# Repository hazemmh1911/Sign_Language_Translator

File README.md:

# Sign_Language_Translator
 
Our team Graduation project ,it uses arduino nano and processing 3 to translate a physical hardware signals into text on an oled and speech in a speaker.

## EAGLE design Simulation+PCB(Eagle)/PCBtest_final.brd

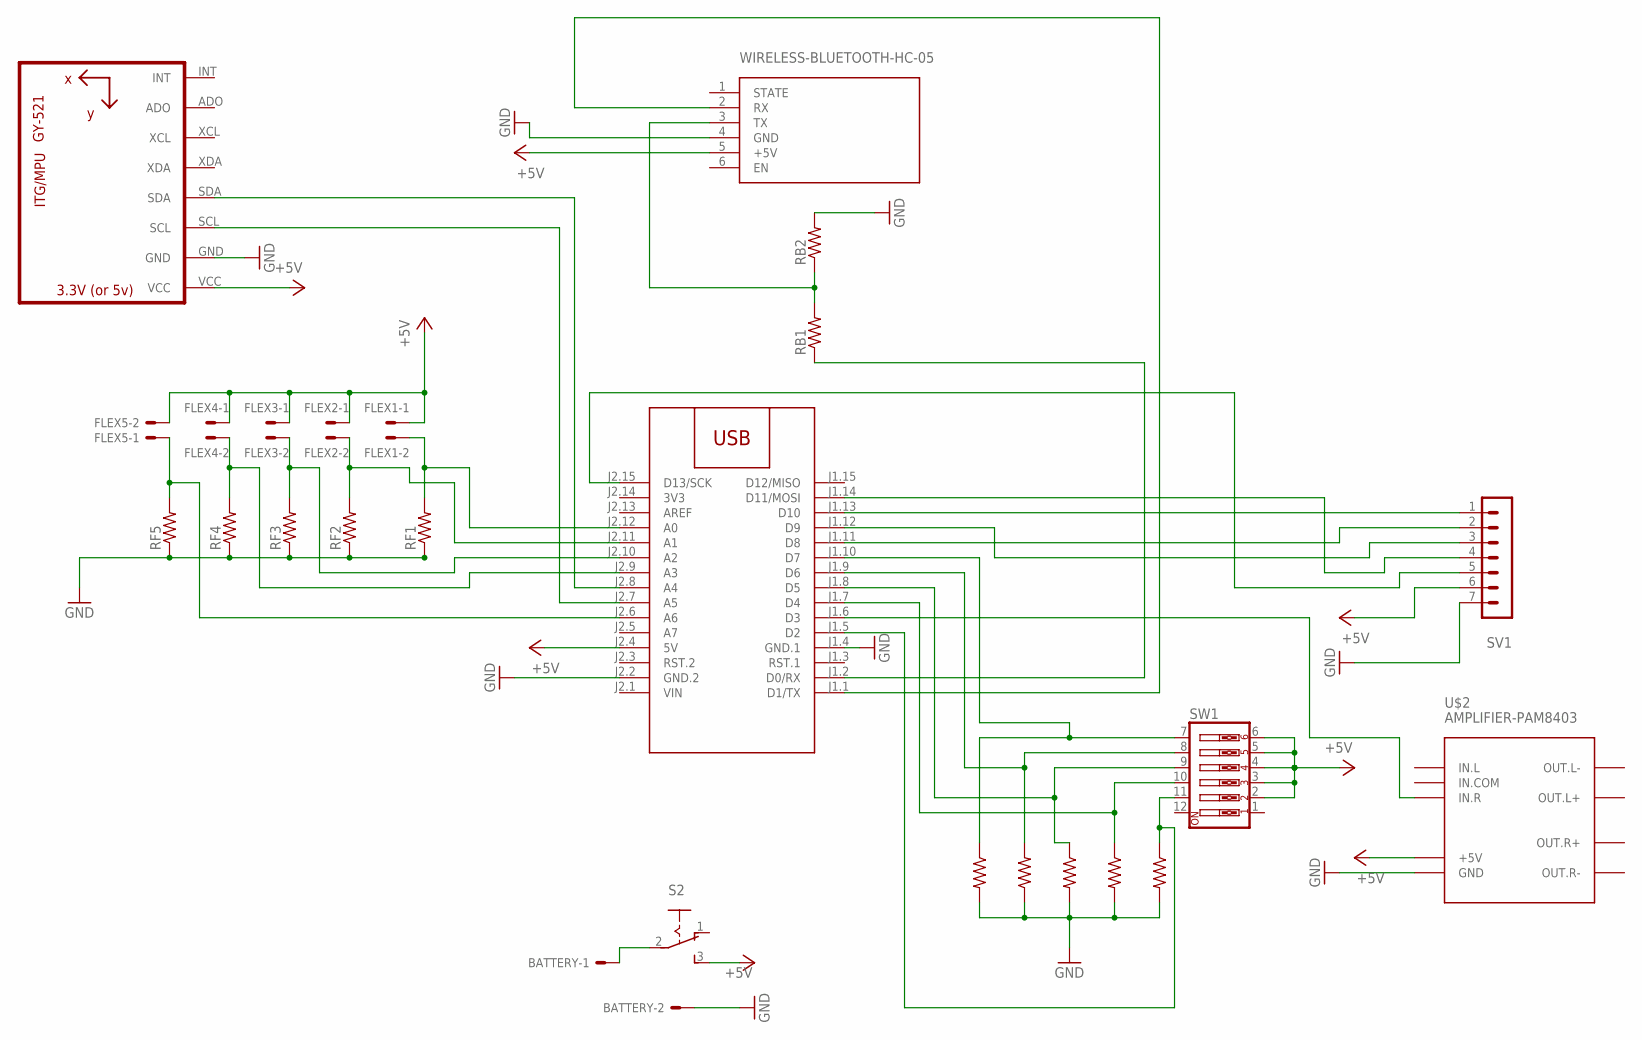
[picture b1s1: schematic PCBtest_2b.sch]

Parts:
BATTERY: 332-02
FLEX1, FLEX2, FLEX3, FLEX4, FLEX5: 332-02
M1: ARDUINO-NANO-3.0
RB1, RB2: R-US_0204/7; 0204/7
RF1, RF2, RF3, RF4, RF5: R-US_0204/7; 0204/7
RS1, RS2, RS3, RS4, RS5: R-US_0204/7; 0204/7
S2: 255SB
SV1: MA07-1
SW1: SW_DIP-6; EDG-06
U1: GY-521MPU6050; GY-521
U$1: WIRELESS-BLUETOOTH-HC-05
U$2: AMPLIFIER-PAM8403

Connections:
3V3: M1.J2.14 (3V3)
+5V: FLEX1.1, FLEX2.1, FLEX3.1, FLEX4.1, FLEX5.2, M1.J2.4 (5V), S2.3 (S), SV1.6, SW1.2, SW1.3, SW1.4, SW1.5, SW1.6, U1.VCC, U$1.5 (+5V), U$2.+5V
GND: BATTERY.2, M1.J1.4 (GND.1), M1.J2.2 (GND.2), RB2.2, RF1.1, RF2.1, RF3.1, RF4.1, RF5.1, RS1.2, RS2.2, RS3.2, RS4.1, RS5.2, SV1.7, U1.GND, U$1.4 (GND), U$2.GND
unnamed: M1.J1.5 (D2), RS1.1, SW1.11
unnamed: FLEX5.1, M1.J2.6 (A6), RF5.2
unnamed: M1.J1.8 (D5), RS3.1, SW1.9
unnamed: FLEX3.2, M1.J2.10 (A2), RF3.2
unnamed: M1.J2.8 (A4), U1.SDA
unnamed: M1.J2.7 (A5), U1.SCL
unnamed: RB1.2, RB2.1, U$1.3 (TX)
unnamed: FLEX1.2, M1.J2.12 (A0), RF1.2
unnamed: M1.J1.6 (D3), U$2.IN.R
unnamed: M1.J1.1 (D1/TX), U$1.2 (RX)
unnamed: M1.J1.2 (D0/RX), RB1.1
unnamed: M1.J1.9 (D6), RS4.2, SW1.8
unnamed: FLEX4.2, M1.J2.9 (A3), RF4.2
unnamed: M1.J1.13 (D10), SV1.1
unnamed: FLEX2.2, M1.J2.11 (A1), RF2.2
unnamed: M1.J1.11 (D8), SV1.2
unnamed: M1.J1.12 (D9), SV1.3
unnamed: BATTERY.1, S2.2
unnamed: M1.J1.14 (D11/MOSI), SV1.4
unnamed: M1.J2.15 (D13/SCK), SV1.5
unnamed: M1.J1.10 (D7), RS5.1, SW1.7
unnamed: M1.J1.7 (D4), RS2.1, SW1.10
VIN: M1.J2.1 (VIN)

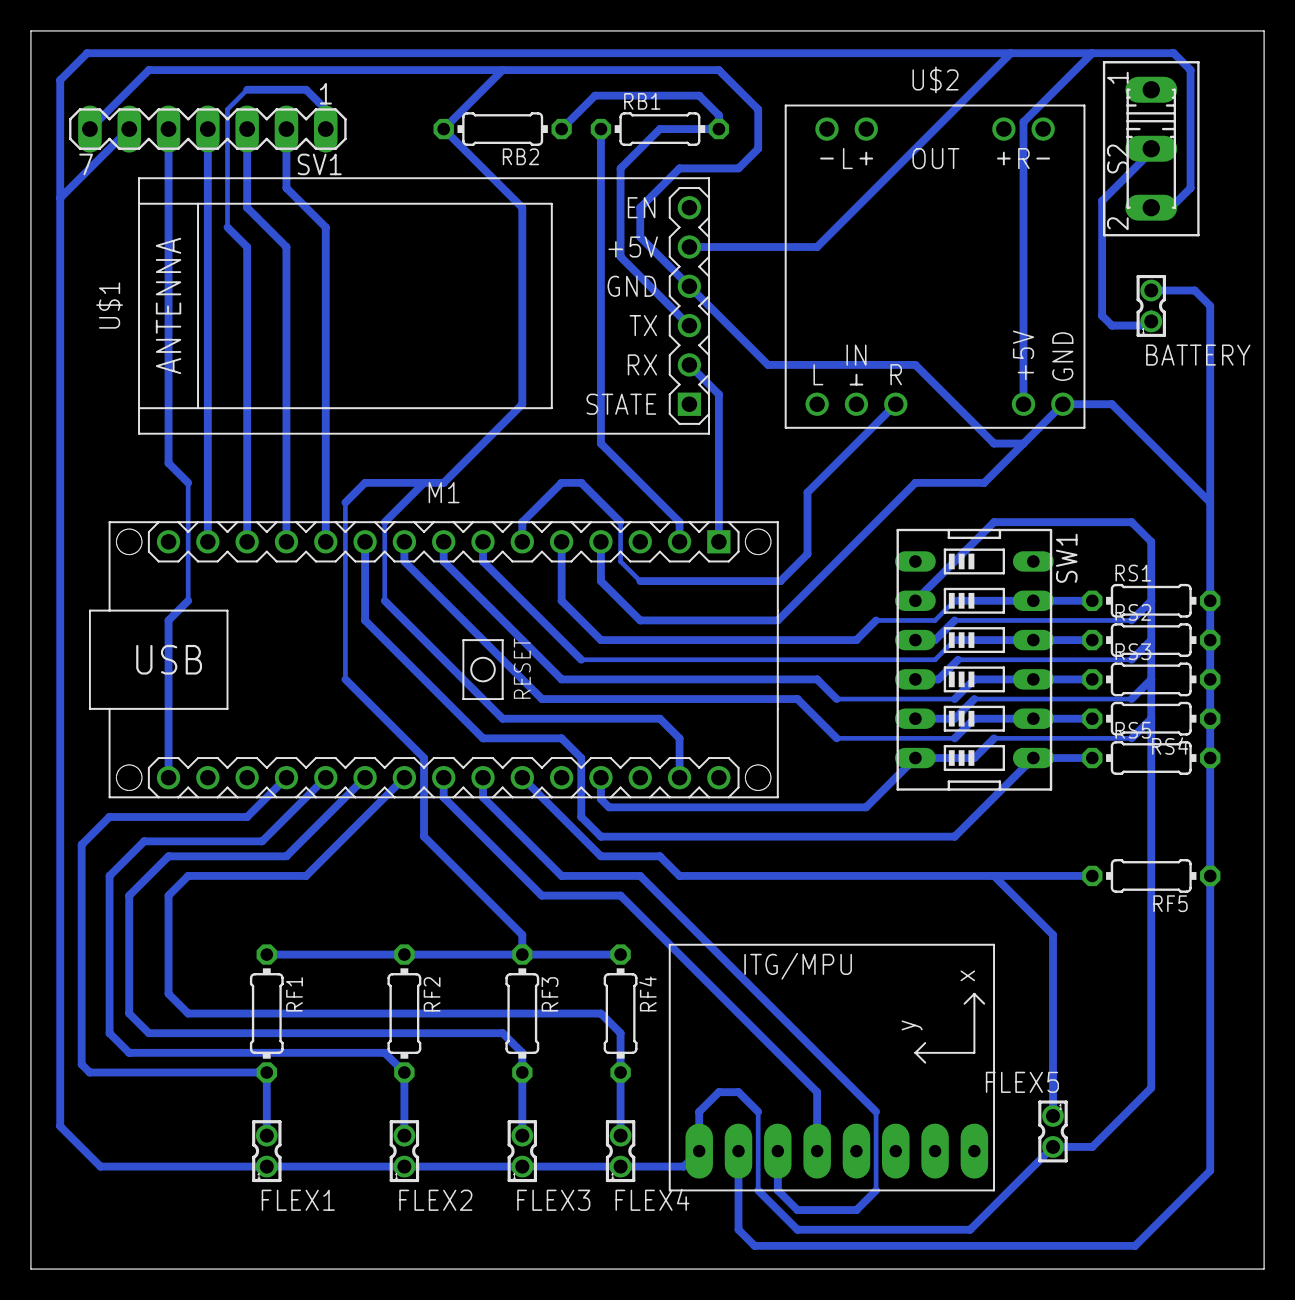
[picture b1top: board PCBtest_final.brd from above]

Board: 2 copper layers, 79.7 x 80.0 mm, 25 parts (0 on the bottom side), 24 nets.

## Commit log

2021-07-25 Last Version
2022-05-26 Ignoreing unwanted Documents

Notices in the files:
parts and their libraries:
diy-modules: Released under the Creative Commons Attribution 4.0 International License: http://creativecommons.org/licenses/by/4.0
